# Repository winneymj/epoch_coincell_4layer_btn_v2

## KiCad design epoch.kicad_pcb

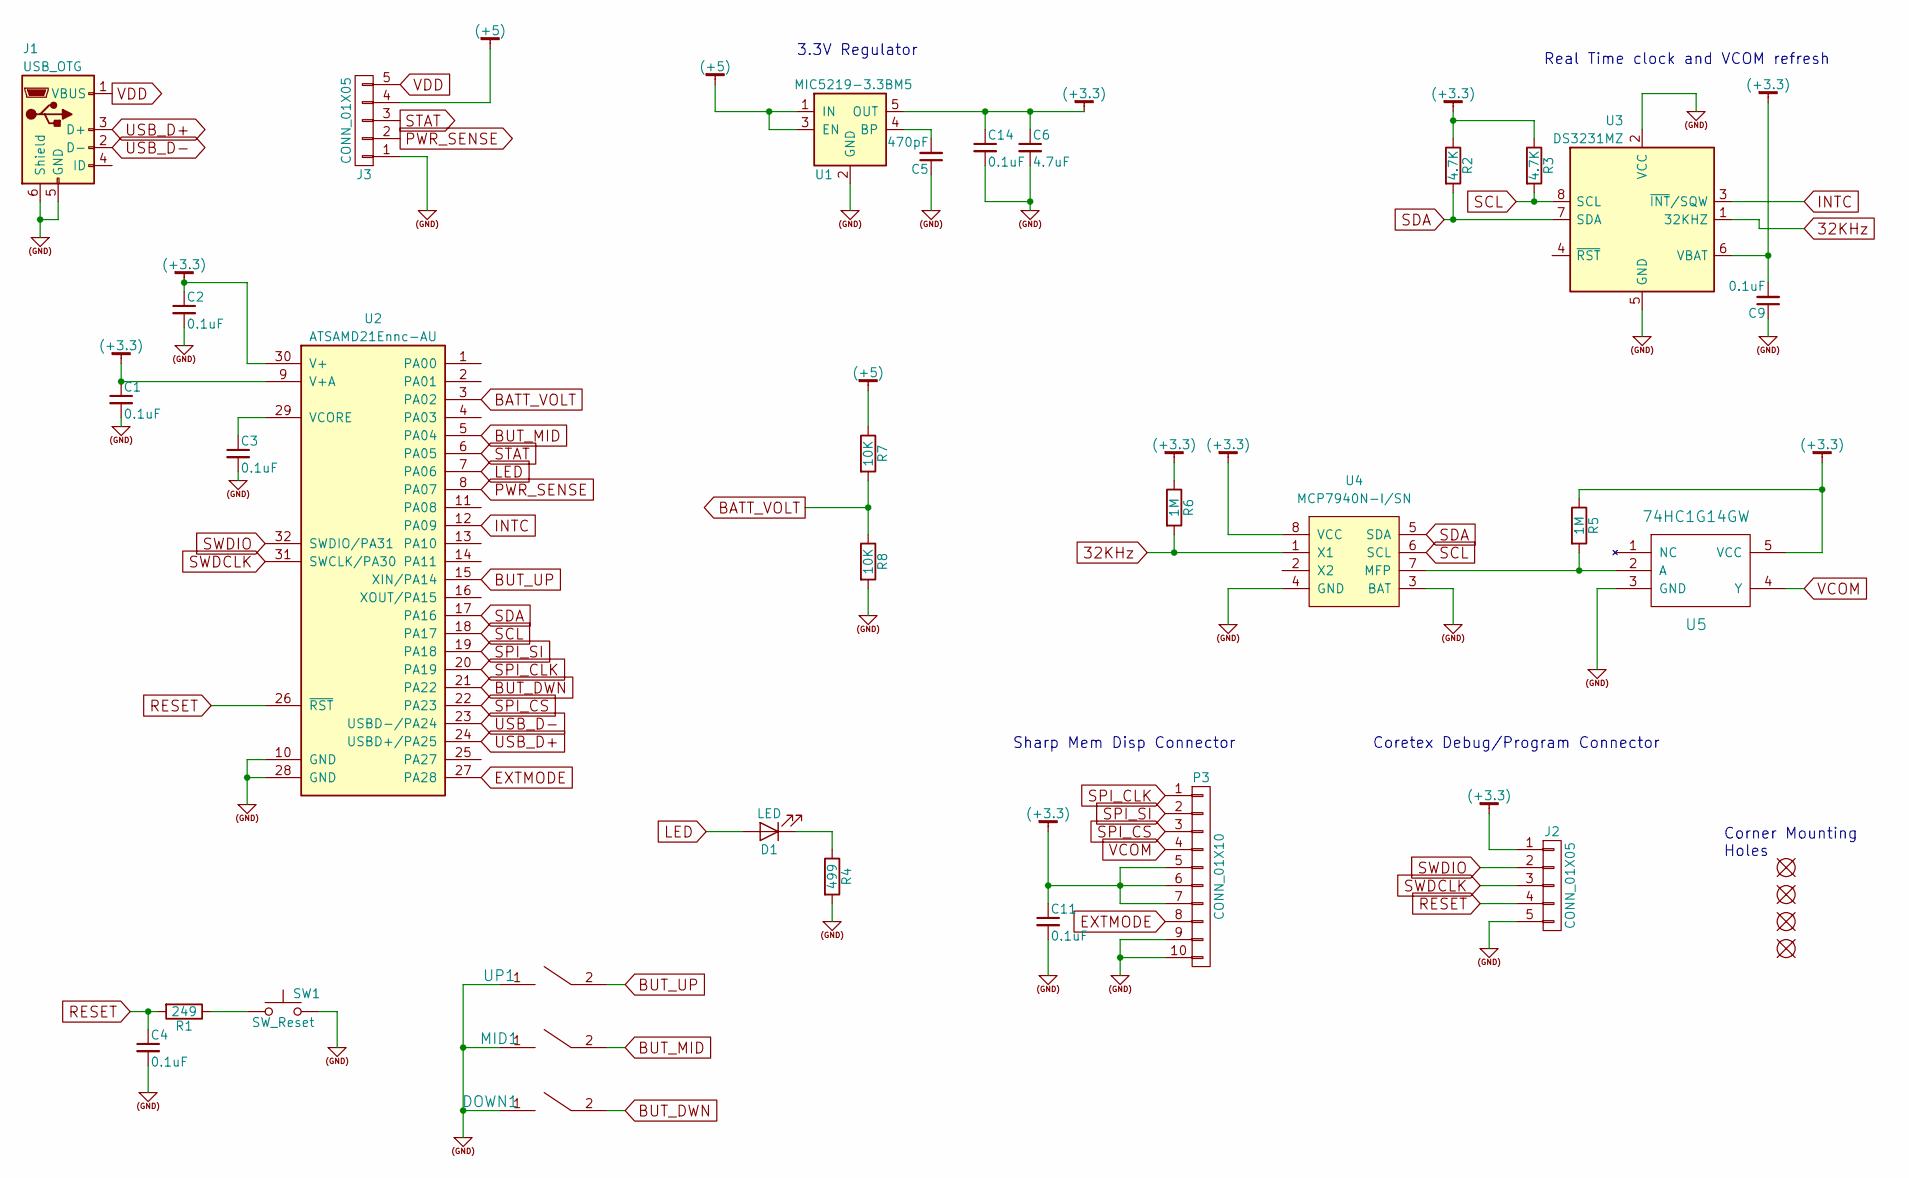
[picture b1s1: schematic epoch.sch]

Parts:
C1, C2, C3, C4, C9, C11, C14: 0.1uF; C_0805_HandSoldering
C5: 470pF; C_0805_HandSoldering
C6: 4.7uF; C_0805_HandSoldering
D1: LED; LED_0805
DOWN1: Tact_SW_3x6x33.5; Tact_SW_3x6x3.5
J1: USB_OTG; USB-MICROB_LARGEPAD
J2: CONN_01X05; Pin_Header_Straight_1x05_Pitch1.27mm
J3: CONN_01X05; Pin_Header_Straight_1x05_Pitch1.27mm_no_silk
MID1: Tact_SW_3x6x33.5; Tact_SW_3x6x3.5
P3: CONN_01X10; MOLEX_0.5MM_505278
R1: 249; R_0805_HandSoldering
R2, R3: 4.7K; R_0805_HandSoldering
R4: 499; R_0805_HandSoldering
R5, R6: 1M; R_0805_HandSoldering
R7, R8: 10K; R_0805_HandSoldering
SW1: SW_Reset; SW_SPST_B3U-3000P
U1: MIC5219-3.3BM5; SOT-23-5
U2: ATSAMD21Ennc-AU; TQFP-32_7x7mm_Pitch0.8mm; MPN ATSAMD21Ennc-AU
U3: DS3231MZ; SOIC-8_3.9x4.9mm_Pitch1.27mm
U4: MCP7940N-I/SN; SOIC-8_3.9x4.9mm_Pitch1.27mm; MPN MCP7940N-I/SN
U5: 74HC1G14GW; SOT-353_SC-70-5_Handsoldering
U6, U7, U8, U9: MH2mm; MH2.1mm
UP1: Tact_SW_3x6x33.5; Tact_SW_3x6x3.5

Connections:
32KHz: R6.2, U3.1 (32KHZ), U4.1 (X1)
(+3.3): C1.1, C2.1, C6.1, C9.2, C11.1, C14.1, J2.1, P3.5, P3.6, P3.7, R2.1, R3.1, R5.1, R6.1, U1.5 (OUT), U2.9 (V+A), U2.30 (V+), U3.6 (VBAT), U4.8 (VCC), U5.5 (VCC)
(+5): J3.4, R7.1, U1.1 (IN), U1.3 (EN)
(GND): C1.2, C2.2, C3.2, C4.2, C5.1, C6.2, C9.1, C11.2, C14.2, DOWN1.1, J1.5 (GND), J1.6 (Shield), J2.5, J3.1, MID1.1, P3.9, P3.10, R4.2, R8.2, SW1.2, U1.2 (GND), U2.10 (GND), U2.28 (GND), U3.2 (VCC), U3.5 (GND), U4.3 (BAT), U4.4 (GND), U5.3 (GND), UP1.1
BATT_VOLT: R7.2, R8.1, U2.3 (PA02)
BUT_DWN: DOWN1.2, U2.21 (PA22)
BUT_MID: MID1.2, U2.5 (PA04)
BUT_UP: U2.15 (XIN/PA14), UP1.2
EXTMODE: P3.8, U2.27 (PA28)
INTC: U2.12 (PA09), U3.3 (~INT~/SQW)
LED: D1.2 (A), U2.7 (PA06)
unnamed: C3.1, U2.29 (VCORE)
unnamed: C5.2, U1.4 (BP)
unnamed: D1.1 (K), R4.1
unnamed: R1.1, SW1.1
unnamed: R5.2, U4.7 (MFP), U5.2 (A)
PWR_SENSE: J3.2, U2.8 (PA07)
RESET: C4.1, J2.4, R1.2, U2.26 (~RST)
SCL: R3.2, U2.18 (PA17), U3.8 (SCL), U4.6 (SCL)
SDA: R2.2, U2.17 (PA16), U3.7 (SDA), U4.5 (SDA)
SPI_CLK: P3.1, U2.20 (PA19)
SPI_CS: P3.3, U2.22 (PA23)
SPI_SI: P3.2, U2.19 (PA18)
STAT: J3.3, U2.6 (PA05)
SWDCLK: J2.3, U2.31 (SWCLK/PA30)
SWDIO: J2.2, U2.32 (SWDIO/PA31)
USB_D+: J1.3 (D+), U2.24 (USBD+/PA25)
USB_D-: J1.2 (D-), U2.23 (USBD-/PA24)
VCOM: P3.4, U5.4 (Y)
VDD: J1.1 (VBUS), J3.5

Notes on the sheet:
Coretex Debug/Program Connector
3.3V Regulator
Sharp Mem Disp Connector
Real Time clock and VCOM refresh
Corner Mounting Holes

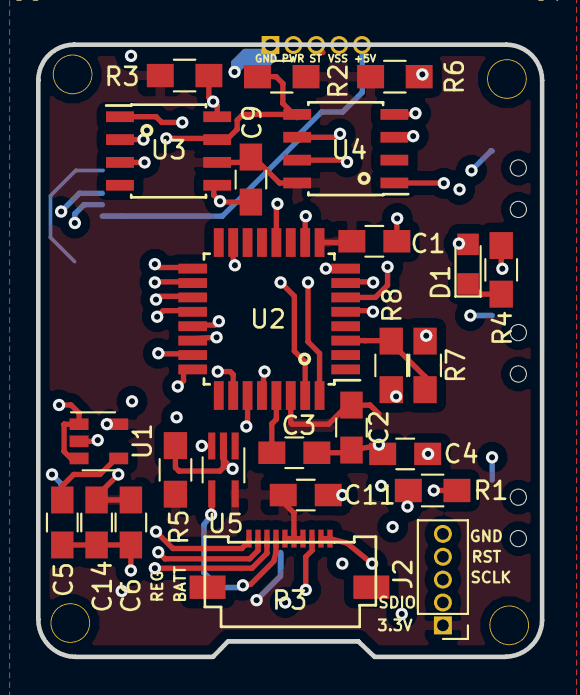
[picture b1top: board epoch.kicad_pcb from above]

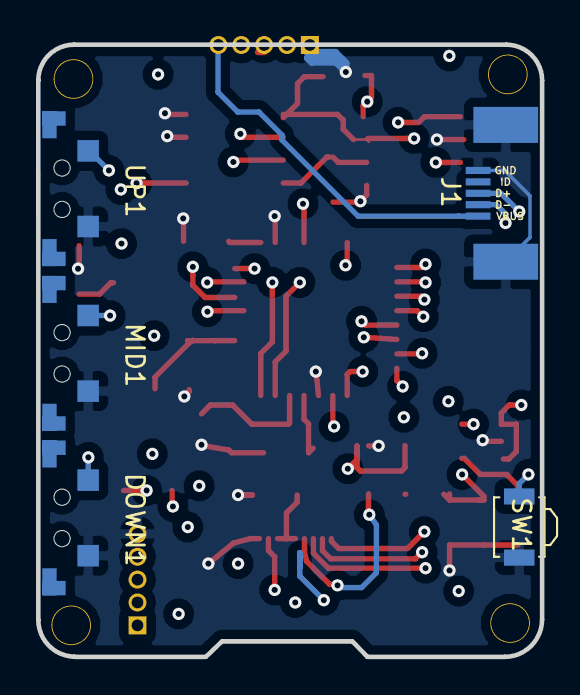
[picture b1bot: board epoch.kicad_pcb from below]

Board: 4 copper layers, 28.0 x 34.0 mm, 35 parts (5 on the bottom side), 30 nets.

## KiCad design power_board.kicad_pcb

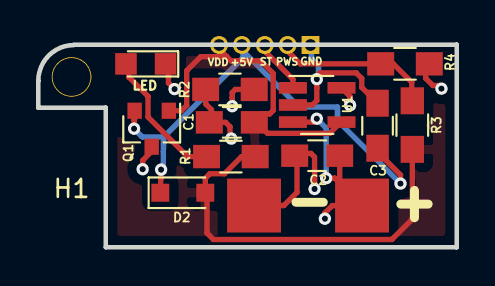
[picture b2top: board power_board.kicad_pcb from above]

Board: 4 copper layers, 23.2 x 11.2 mm, 14 parts (1 on the bottom side), 8 nets.

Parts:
C1, C2: 4.7uF; C_0805_HandSoldering
C3: 1uF; C_0805_HandSoldering
D2: ZLLS410; D_SOD-323_HandSoldering
H1: MH2.1mm
J1: CONN_01X05; Pin_Header_Straight_1x05_Pitch1.27mm
LED: LED; LED_0805
P1: BATT; Battery Pads 3x3
Q1: Q_PMOS_GSD (DMP1045U); SOT-23
R1: 220; R_0805_HandSoldering
R2: 5K6; R_0805_HandSoldering
R3, R4: 47K; R_0805_HandSoldering
U1: MCP73831T-2ACI_OT; SOT-23-5_HandSoldering

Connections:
(GND): C1.2, C2.2, C3.2, J1.1, P1.2, R2.2, R4.1, U1.2
+5V: C3.1, D2.1, J1.4, Q1.2
/D: C2.1, P1.1, Q1.3, U1.3
unnamed: LED.2, R1.2
unnamed: R2.1, U1.5
PWR_SENSE: J1.2, R3.1, R4.2
STAT: J1.3, LED.1, U1.1
VDD: C1.1, D2.2, J1.5, Q1.1, R1.1, R3.2, U1.4

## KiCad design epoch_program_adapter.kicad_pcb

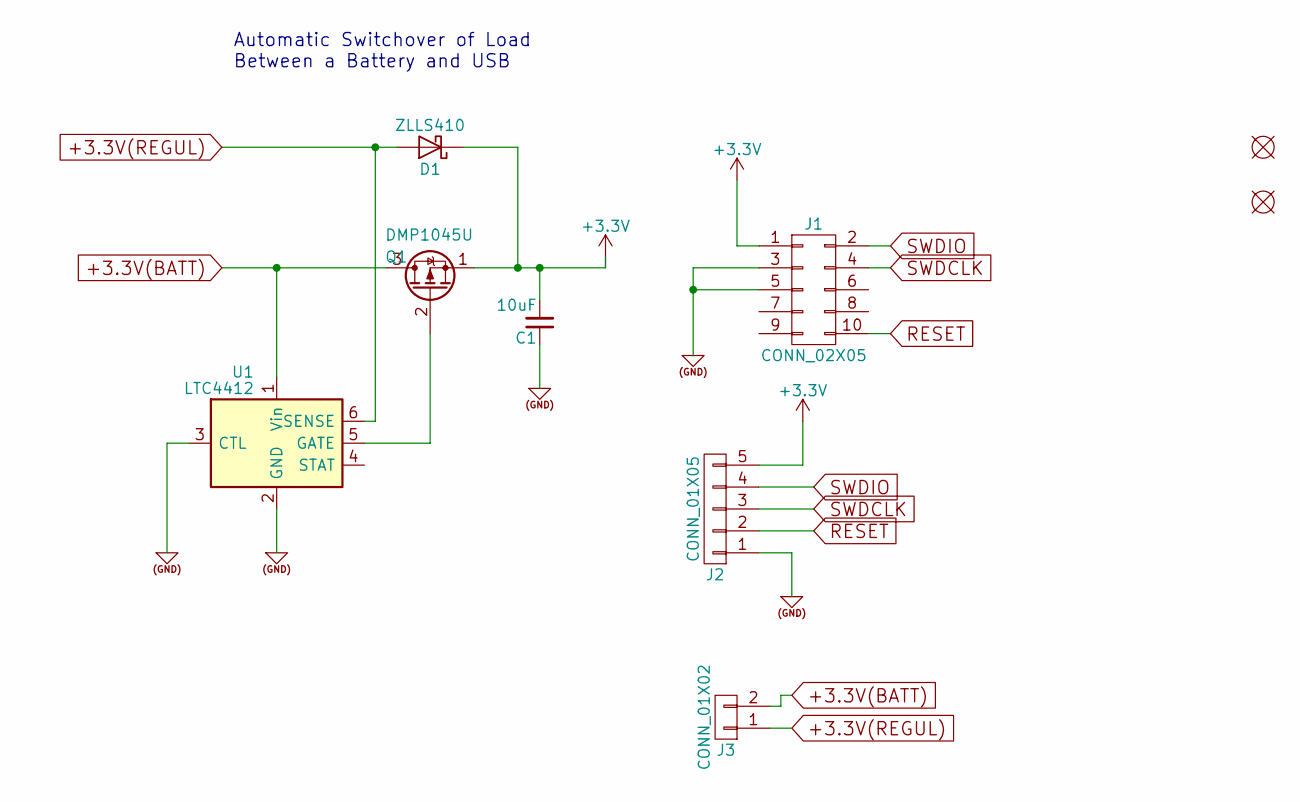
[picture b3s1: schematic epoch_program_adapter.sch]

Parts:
C1: 10uF; C_0805_HandSoldering
D1: ZLLS410; D_SOD-323_HandSoldering
H1, H2: MH2mm; MH2.1mm
J1: CONN_02X05; Pin_Header_Straight_2x05_Pitch1.27mm
J2: CONN_01X05; Pin_Header_Straight_1x05_Pitch1.27mm
J3: CONN_01X02; Pin_Header_Straight_1x02_Pitch1.27mm
Q1: DMP1045U; TSOT-23_HandSoldering
U1: LTC4412; SOT-23-6_Handsoldering

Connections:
(GND): C1.1, J1.3, J1.5, J2.1, U1.2 (GND), U1.3 (CTL)
+3.3V(BATT): J3.2, Q1.3 (D), U1.1 (Vin)
+3.3V(REGUL): D1.2 (A), J3.1, U1.6 (SENSE)
+3V3: C1.2, D1.1 (K), J1.1, J2.5, Q1.1 (S)
unnamed: Q1.2 (G), U1.5 (GATE)
RESET: J1.10, J2.2
SWDCLK: J1.4, J2.3
SWDIO: J1.2, J2.4

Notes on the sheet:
Automatic Switchover of Load Between a Battery and USB

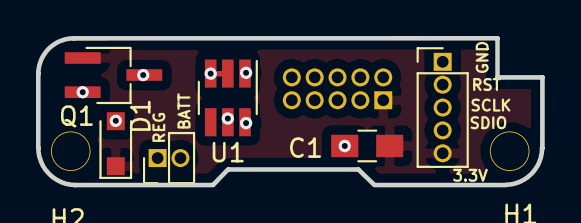
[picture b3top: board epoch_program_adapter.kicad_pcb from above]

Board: 4 copper layers, 28.0 x 8.2 mm, 9 parts (1 on the bottom side), 8 nets.

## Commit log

2018-10-12 Initial commit for V2 - This will not have the extra board connectors that would allow programming when coin cell is present (never developed or proved)
2018-10-12 Remove connector and redo the connections
2018-12-30 Update for LIPO power_board
2019-02-23 New connections to power board
2019-02-23 Fix ground plane
2019-03-21 Update for voltage divider to get battery level
